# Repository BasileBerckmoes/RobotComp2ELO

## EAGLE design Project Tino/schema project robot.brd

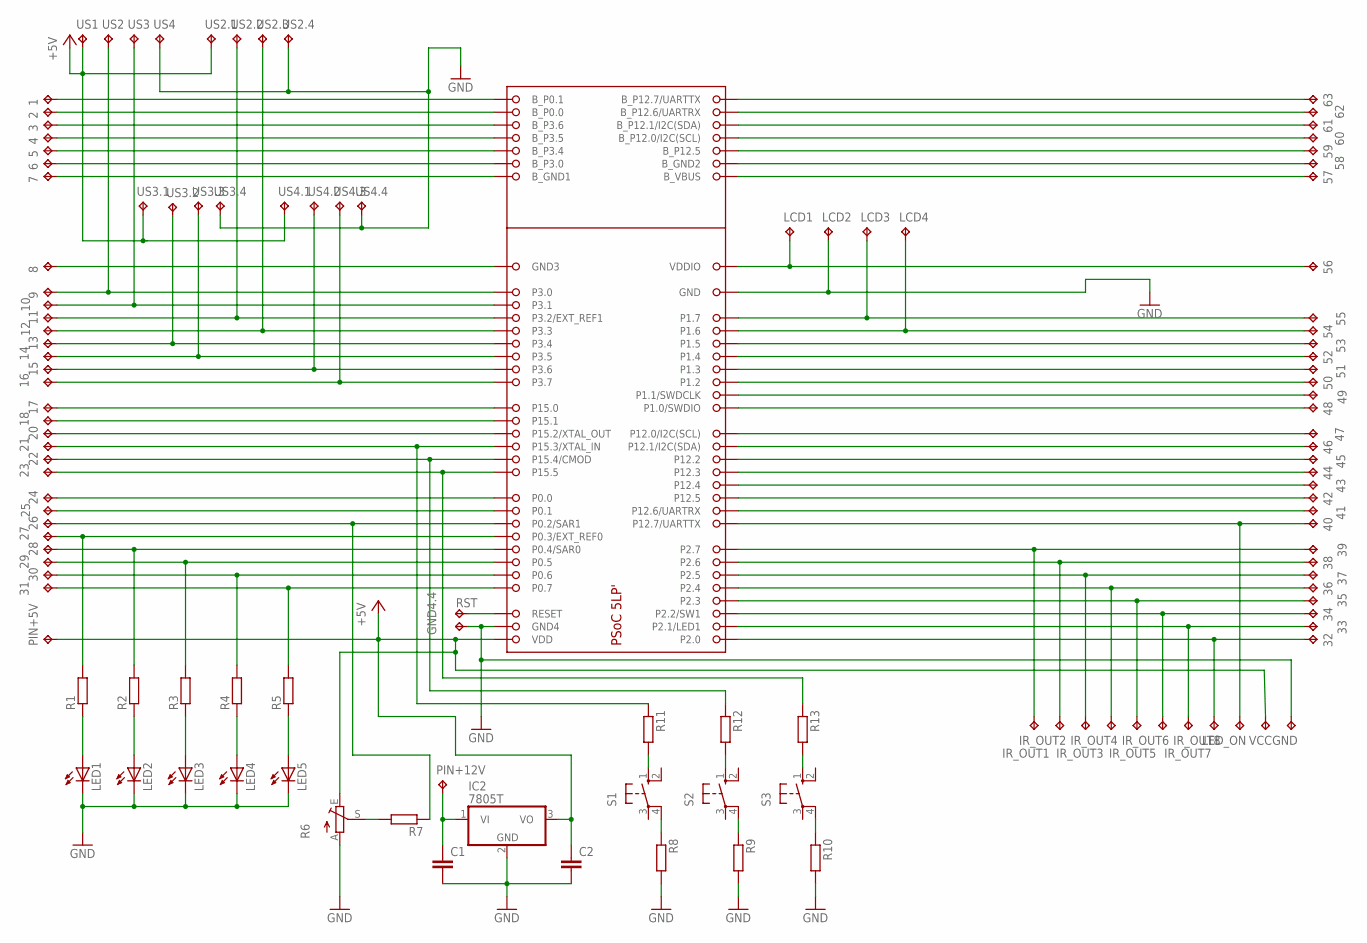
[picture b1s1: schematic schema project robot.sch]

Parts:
1, 2, 3, 4, 5, 6, 7, 8, 9, 10, 11, 12, 13, 14, 15, 16, 17, 18, 20, 21, 22, 23, 24, 25, 26, 27, 28, 29, 30, 31, 32, 33, 34, 35, 36, 37, 38, 39, 40, 41, 42, 43, 44, 45, 46, 47, 48, 49, 50, 51, 52, 53, 54, 55, 56, 57, 58, 59, 60, 61, 62, 63: TPPAD1-13Y; P1-13Y
C1, C2: C-EU050-035X075; C050-035X075
DEVICE1: CYPRESSFOOTPRINT_CYPRESS; CYPRESSFOOTPRINT_CYPRESSFOOTPRINT
GND, GND4.4: TPPAD1-13Y; P1-13Y
IC2: 7805T; TO220H
IR_OUT1, IR_OUT2, IR_OUT3, IR_OUT4, IR_OUT5, IR_OUT6, IR_OUT7, IR_OUT8: TPPAD1-13Y; P1-13Y
LCD1, LCD2, LCD3, LCD4: TPPAD1-13Y; P1-13Y
LED1, LED2, LED3, LED4, LED5: LED5MM
LED_ON: TPPAD1-13Y; P1-13Y
PIN+5V, PIN+12V: TPPAD1-13Y; P1-13Y
R1, R2, R3, R4, R5, R7, R8, R9, R10, R11, R12, R13: R-EU_0204/7; 0204/7
R6: TRIM_EU-CIP20C-6MM; CIP20C-6MM
RST: TPPAD1-13Y; P1-13Y
S1, S2, S3: 10-XX; B3F-10XX
US1, US2, US2.1, US2.2, US2.3, US2.4, US3, US3.1, US3.2, US3.3, US3.4, US4, US4.1, US4.2, US4.3, US4.4: TPPAD1-13Y; P1-13Y
VCC: TPPAD1-13Y; P1-13Y

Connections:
+5V: C2.1, DEVICE1.VVD (VDD), IC2.3 (VO), PIN+5V.TP, R6.E, US1.TP, US2.1.TP, US3.1.TP, US4.1.TP, VCC.TP
GND: C1.2, C2.2, DEVICE1.GND, DEVICE1.GND4, GND.TP, GND4.4.TP, IC2.2 (GND), LCD2.TP, LED1.K (C), LED2.K (C), LED3.K (C), LED4.K (C), LED5.K (C), R6.A, R8.2, R9.2, R10.2, US2.4.TP, US3.4.TP, US4.TP, US4.4.TP
unnamed: LED1.A, R1.1
unnamed: LED2.A, R2.1
unnamed: LED3.A, R3.1
unnamed: LED4.A, R4.1
unnamed: LED5.A, R5.1
unnamed: 31.TP, DEVICE1.P0.7, R5.2
unnamed: 30.TP, DEVICE1.P0.6, R4.2
unnamed: 29.TP, DEVICE1.P0.5, R3.2
unnamed: 25.TP, DEVICE1.P0.1
unnamed: 24.TP, DEVICE1.P0.0
unnamed: 1.TP, DEVICE1.B_P0.1
unnamed: 2.TP, DEVICE1.B_P0.0
unnamed: 3.TP, DEVICE1.B_P3.6
unnamed: 4.TP, DEVICE1.B_P3.5
unnamed: 5.TP, DEVICE1.B_P3.4
unnamed: 6.TP, DEVICE1.B_P3.0
unnamed: 7.TP, DEVICE1.B_GND1
unnamed: 8.TP, DEVICE1.GND3
unnamed: 9.TP, DEVICE1.P3.0, US2.TP
unnamed: 10.TP, DEVICE1.P3.1, US3.TP
unnamed: 11.TP, DEVICE1.P3.2 (P3.2/EXT_REF1), US2.2.TP
unnamed: 12.TP, DEVICE1.P3.3, US2.3.TP
unnamed: 16.TP, DEVICE1.P3.7, US4.3.TP
unnamed: 15.TP, DEVICE1.P3.6, US4.2.TP
unnamed: C1.1, IC2.1 (VI), PIN+12V.TP
unnamed: 14.TP, DEVICE1.P3.5, US3.3.TP
unnamed: 17.TP, DEVICE1.P15.0
unnamed: 18.TP, DEVICE1.P15.1
unnamed: 20.TP, DEVICE1.P15.2/XTAL_OUT
unnamed: 21.TP, DEVICE1.P15.3/XTAL_IN, R11.1
unnamed: 22.TP, DEVICE1.P15.4/CMOD, R12.1
unnamed: 23.TP, DEVICE1.P15.5, R13.1
unnamed: 26.TP, DEVICE1.P0.2/SAR1, R7.1
unnamed: 27.TP, DEVICE1.P0.3/EXT_REF0, R1.2
unnamed: 28.TP, DEVICE1.P0.4/SAR0, R2.2
unnamed: DEVICE1.RESET, RST.TP
unnamed: 13.TP, DEVICE1.P3.4, US3.2.TP
unnamed: 32.TP, DEVICE1.P2.0, IR_OUT8.TP
unnamed: 33.TP, DEVICE1.P2.1/LED1, IR_OUT7.TP
unnamed: 34.TP, DEVICE1.P2.2/SW1, IR_OUT6.TP
unnamed: 35.TP, DEVICE1.P2.3, IR_OUT5.TP
unnamed: 36.TP, DEVICE1.P2.4, IR_OUT4.TP
unnamed: 37.TP, DEVICE1.P2.5, IR_OUT3.TP
unnamed: 38.TP, DEVICE1.P2.6, IR_OUT2.TP
unnamed: 39.TP, DEVICE1.P2.7, IR_OUT1.TP
unnamed: 40.TP, DEVICE1.P12.7/UARTTX, LED_ON.TP
unnamed: 41.TP, DEVICE1.P12.6/UARTRX
unnamed: 42.TP, DEVICE1.P12.5
unnamed: 43.TP, DEVICE1.P12.4
unnamed: 44.TP, DEVICE1.P12.3
unnamed: 45.TP, DEVICE1.P12.2
unnamed: 46.TP, DEVICE1.P12.1/I2C(SDA)
unnamed: 47.TP, DEVICE1.P12.0/I2C(SCL)
unnamed: 48.TP, DEVICE1.P1.0/SWDIO
unnamed: 49.TP, DEVICE1.P1.1/SWDCLK
unnamed: 50.TP, DEVICE1.P1.2
unnamed: 51.TP, DEVICE1.P1.3
unnamed: 52.TP, DEVICE1.P1.4
unnamed: 53.TP, DEVICE1.P1.5
unnamed: 54.TP, DEVICE1.P1.6, LCD4.TP
unnamed: 55.TP, DEVICE1.P1.7, LCD3.TP
unnamed: R6.S, R7.2
unnamed: 57.TP, DEVICE1.B_VBUS
unnamed: 58.TP, DEVICE1.B_GND2
unnamed: 59.TP, DEVICE1.B_P12.5
unnamed: 60.TP, DEVICE1.B_12.0/I2C(SCL) (B_P12.0/I2C(SCL))
unnamed: 61.TP, DEVICE1.B_12.1/I2C(SDA) (B_P12.1/I2C(SDA))
unnamed: 62.TP, DEVICE1.B_12.6/UARTRX (B_P12.6/UARTRX)
unnamed: 63.TP, DEVICE1.B_12.7/UARTTX (B_P12.7/UARTTX)
unnamed: R8.1, S1.4 (P1)
unnamed: R9.1, S2.4 (P1)
unnamed: R10.1, S3.4 (P1)
unnamed: R13.2, S3.1 (S)
unnamed: R12.2, S2.1 (S)
unnamed: R11.2, S1.1 (S)
unnamed: 56.TP, DEVICE1.VDDIO, LCD1.TP

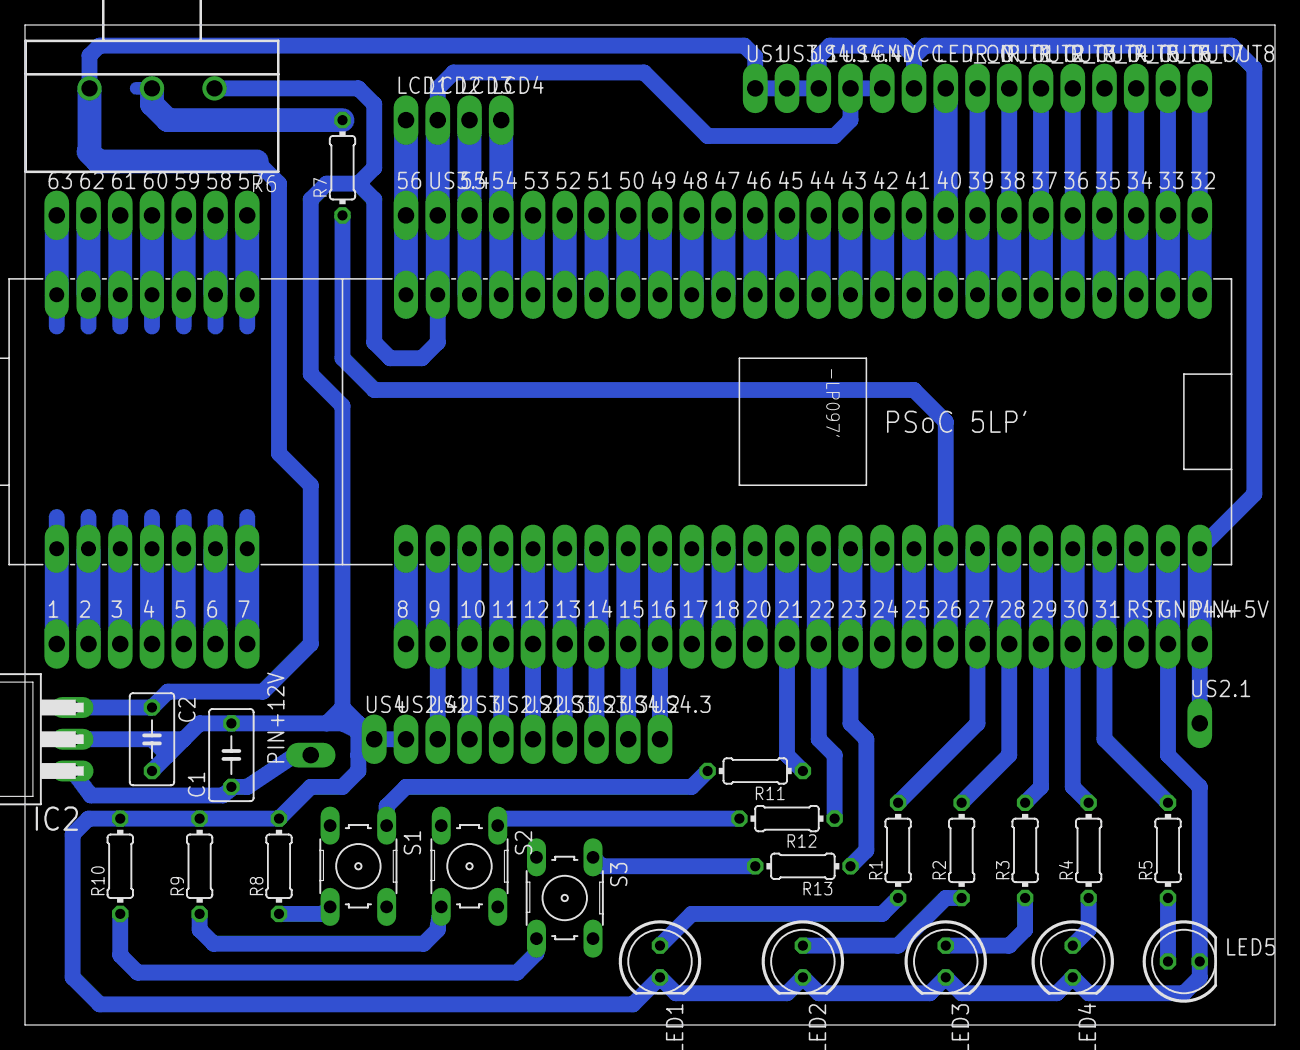
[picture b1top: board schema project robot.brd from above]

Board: 2 copper layers, 100.0 x 80.0 mm, 122 parts (0 on the bottom side), 78 nets.

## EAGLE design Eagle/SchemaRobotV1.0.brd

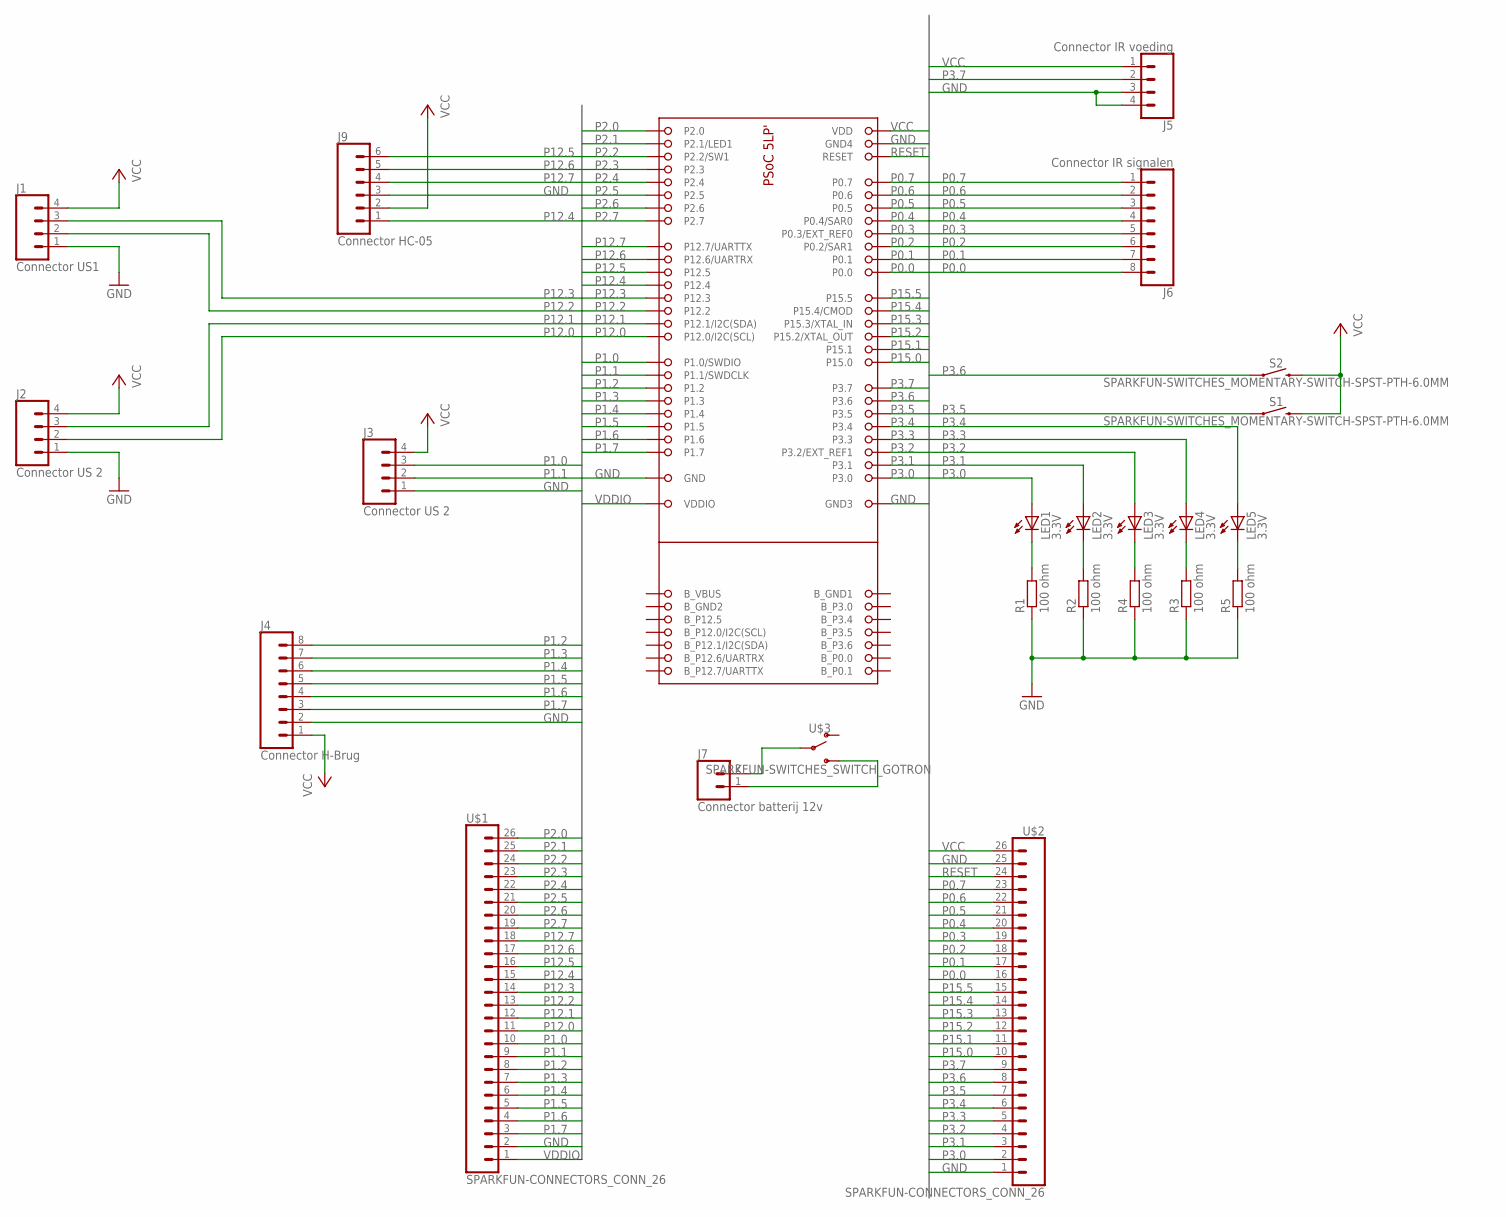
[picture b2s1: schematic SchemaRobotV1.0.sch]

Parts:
DEVICE1: CYPRESSFOOTPRINT_CYPRESS; CYPRESSFOOTPRINT_CYPRESSFOOTPRINT
J1: Connector US1; SPARKFUN-CONNECTORS_SCREWTERMINAL-3.5MM-4
J2, J3: Connector US 2; SPARKFUN-CONNECTORS_SCREWTERMINAL-3.5MM-4
J4: Connector H-Brug; SPARKFUN-CONNECTORS_SCREWTERMINAL-3.5MM-8
J5: Connector IR voeding; SPARKFUN-CONNECTORS_SCREWTERMINAL-3.5MM-4
J6: Connector IR signalen; SPARKFUN-CONNECTORS_SCREWTERMINAL-3.5MM-8
J7: Connector batterij 12v; SPARKFUN-CONNECTORS_SCREWTERMINAL-3.5MM-2
J9: Connector HC-05; SPARKFUN-CONNECTORS_1X06_LONGPADS
LED1, LED3, LED4, LED5: 3.3V; LED_LED5MM
LED2: 3.3V; LED5MM
R1, R2, R3, R4, R5: 100 ohm; EAGLE-LTSPICE_0204/7
S1, S2: SPARKFUN-SWITCHES_MOMENTARY-SWITCH-SPST-PTH-6.0MM; SPARKFUN-SWITCHES_TACTILE_SWITCH_PTH_6.0MM
U$1, U$2: SPARKFUN-CONNECTORS_CONN_26; SPARKFUN-CONNECTORS_1X26
U$3: SPARKFUN-SWITCHES_SWITCH_GOTRON; SPARKFUN-SWITCHES_SWITCH_SPDT_PTH_11.6X5.60MM

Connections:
GND: DEVICE1.GND, DEVICE1.GND3, DEVICE1.GND4, J1.1, J2.1, J3.1, J4.2, J5.3, J5.4, J9.3, R1.1, R2.1, R3.1, R4.1, R5.1, U$1.2, U$2.1, U$2.25
unnamed: J7.2, U$3.2
unnamed: LED1.K (C), R1.2
unnamed: LED2.K (C), R2.2
unnamed: LED3.K (C), R4.2
unnamed: LED4.K (C), R3.2
unnamed: LED5.K (C), R5.2
unnamed: J7.1, U$3.3 (S)
P0.0: DEVICE1.P0.0, J6.8, U$2.16
P0.1: DEVICE1.P0.1, J6.7, U$2.17
P0.2: DEVICE1.P0.2/SAR1, J6.6, U$2.18
P0.3: DEVICE1.P0.3/EXT_REF0, J6.5, U$2.19
P0.4: DEVICE1.P0.4/SAR0, J6.4, U$2.20
P0.5: DEVICE1.P0.5, J6.3, U$2.21
P0.6: DEVICE1.P0.6, J6.2, U$2.22
P0.7: DEVICE1.P0.7, J6.1, U$2.23
P1.0: DEVICE1.P1.0/SWDIO, J3.3, U$1.10
P1.1: DEVICE1.P1.1/SWDCLK, J3.2, U$1.9
P1.2: DEVICE1.P1.2, J4.8, U$1.8
P1.3: DEVICE1.P1.3, J4.7, U$1.7
P1.4: DEVICE1.P1.4, J4.6, U$1.6
P1.5: DEVICE1.P1.5, J4.5, U$1.5
P1.6: DEVICE1.P1.6, J4.4, U$1.4
P1.7: DEVICE1.P1.7, J4.3, U$1.3
P2.0: DEVICE1.P2.0, U$1.26
P2.1: DEVICE1.P2.1/LED1, U$1.25
P2.2: DEVICE1.P2.2/SW1, U$1.24
P2.3: DEVICE1.P2.3, U$1.23
P2.4: DEVICE1.P2.4, U$1.22
P2.5: DEVICE1.P2.5, U$1.21
P2.6: DEVICE1.P2.6, U$1.20
P2.7: DEVICE1.P2.7, U$1.19
P3.0: DEVICE1.P3.0, LED1.A, U$2.2
P3.1: DEVICE1.P3.1, LED2.A, U$2.3
P3.2: DEVICE1.P3.2 (P3.2/EXT_REF1), LED3.A, U$2.4
P3.3: DEVICE1.P3.3, LED4.A, U$2.5
P3.4: DEVICE1.P3.4, LED5.A, U$2.6
P3.5: DEVICE1.P3.5, S1.1, U$2.7
P3.6: DEVICE1.P3.6, S2.1, U$2.8
P3.7: DEVICE1.P3.7, J5.2, U$2.9
P12.0: DEVICE1.P12.0/I2C(SCL), J2.2, U$1.11
P12.1: DEVICE1.P12.1/I2C(SDA), J2.3, U$1.12
P12.2: DEVICE1.P12.2, J1.2, U$1.13
P12.3: DEVICE1.P12.3, J1.3, U$1.14
P12.4: DEVICE1.P12.4, J9.1, U$1.15
P12.5: DEVICE1.P12.5, J9.6, U$1.16
P12.6: DEVICE1.P12.6/UARTRX, J9.5, U$1.17
P12.7: DEVICE1.P12.7/UARTTX, J9.4, U$1.18
P15.0: DEVICE1.P15.0, U$2.10
P15.1: DEVICE1.P15.1, U$2.11
P15.2: DEVICE1.P15.2/XTAL_OUT, U$2.12
P15.3: DEVICE1.P15.3/XTAL_IN, U$2.13
P15.4: DEVICE1.P15.4/CMOD, U$2.14
P15.5: DEVICE1.P15.5, U$2.15
RESET: DEVICE1.RESET, U$2.24
VCC: DEVICE1.VVD (VDD), J1.4, J2.4, J3.4, J4.1, J5.1, J9.2, S1.3 (2), S2.3 (2), U$2.26
VDDIO: DEVICE1.VDDIO, U$1.1

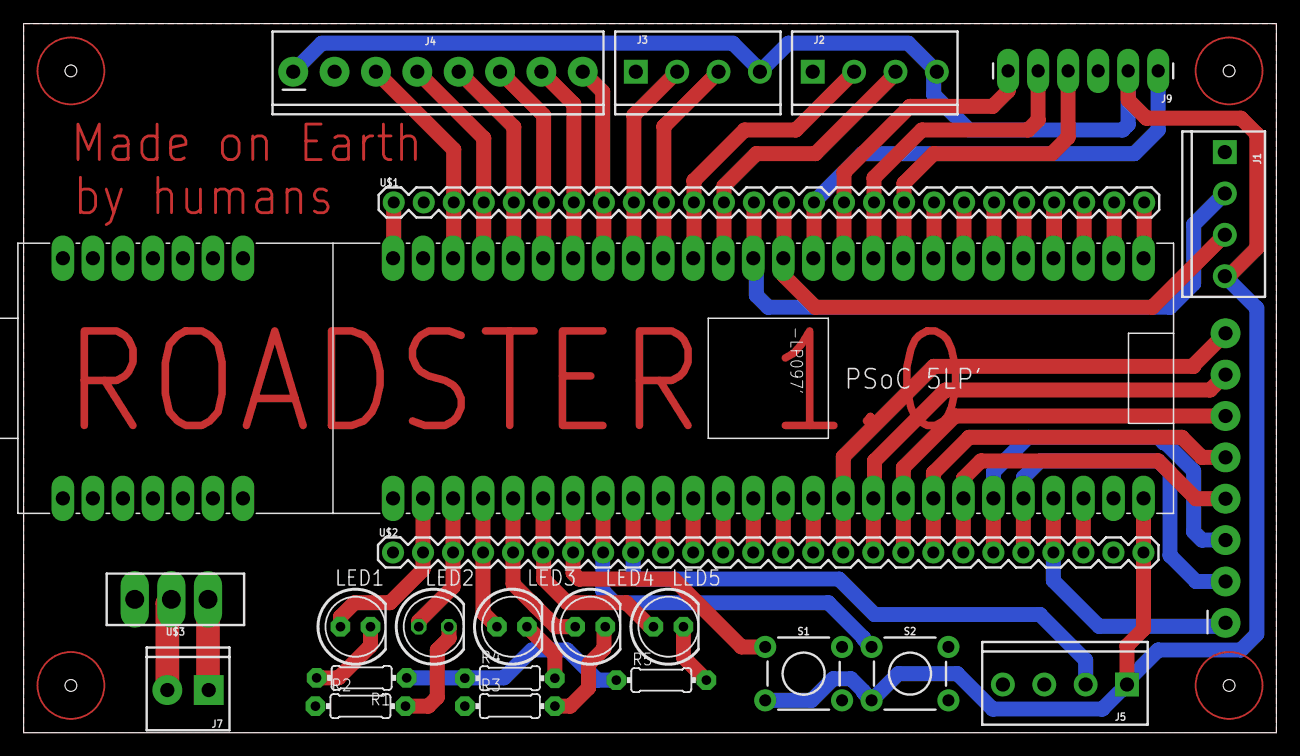
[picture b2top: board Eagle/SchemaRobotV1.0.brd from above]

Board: 2 copper layers, 106.0 x 60.0 mm, 24 parts (1 on the bottom side), 57 nets.

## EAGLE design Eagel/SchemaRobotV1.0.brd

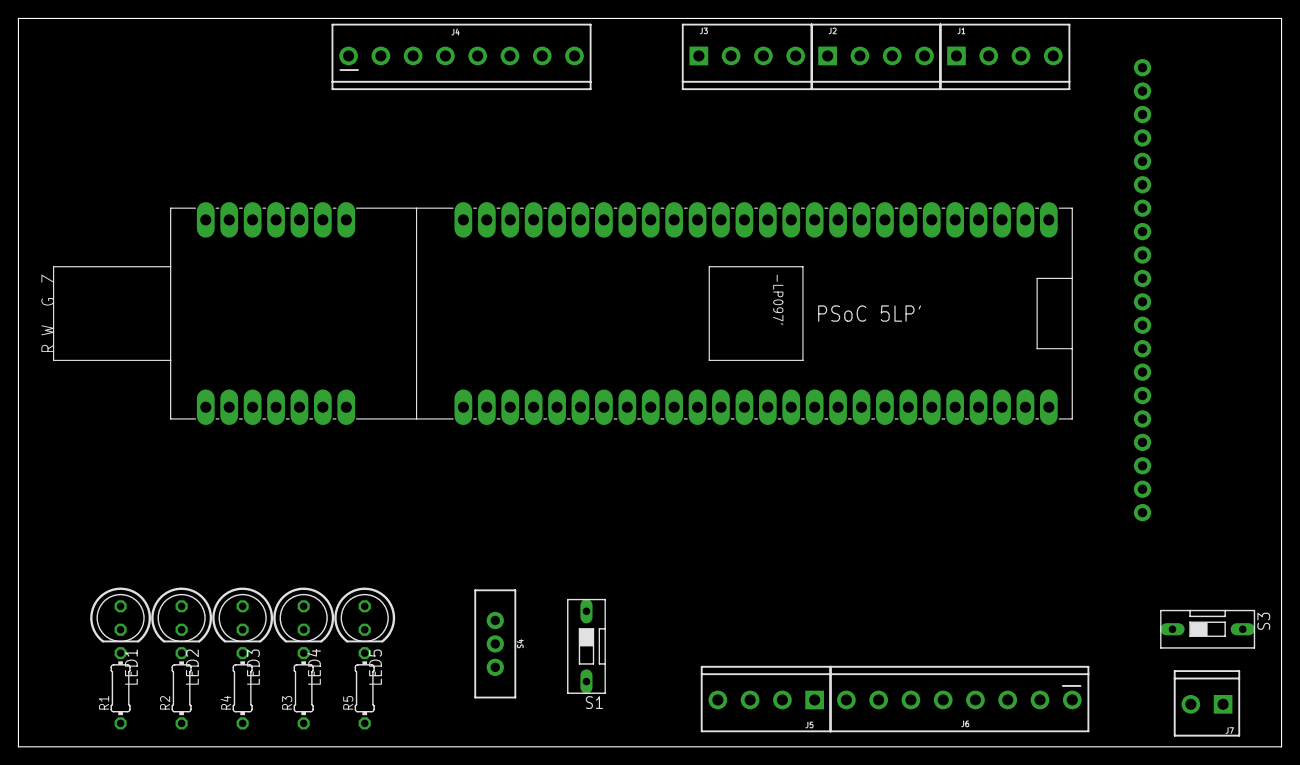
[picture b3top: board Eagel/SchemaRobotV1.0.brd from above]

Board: 2 copper layers, 137.0 x 79.0 mm, 22 parts (1 on the bottom side), 44 nets, no tracks yet.

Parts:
DEVICE1: CYPRESSFOOTPRINT_CYPRESS; CYPRESSFOOTPRINT_CYPRESSFOOTPRINT
J1: Connector US1; SCREWTERMINAL-3.5MM-4
J2, J3: Connector US 2; SCREWTERMINAL-3.5MM-4
J4: Connector H-Brug; SCREWTERMINAL-3.5MM-8
J5: Connector IR voeding; SCREWTERMINAL-3.5MM-4
J6: Connector IR signalen; SCREWTERMINAL-3.5MM-8
J7: Connector batterij 12v; SCREWTERMINAL-3.5MM-2
J8: Connector LCD; 1X20
LED1, LED2, LED3, LED4, LED5: LED5MM
R1, R2, R3, R4, R5: 100 ohm; 0204/7
S1, S3: DS-01
S4: SWITCH_SPDT_PTH_11.6X4.0MM

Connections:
ECHO1: DEVICE1.P12.3, J1.3
ECHO2: DEVICE1.P12.1/I2C(SDA), J2.3
ECHO3: DEVICE1.P1.0/SWDIO, J3.3
ENA: DEVICE1.P1.2, J4.8
ENB: DEVICE1.P1.7, J4.3
GND: DEVICE1.GND, DEVICE1.GND3, DEVICE1.GND4, J1.1, J2.1, J3.1, J4.2, J5.3, J5.4, J8.1, J8.3, R1.1, R2.1, R3.1, R4.1, R5.1, S4.3
IN1: DEVICE1.P1.3, J4.7
IN2: DEVICE1.P1.4, J4.6
IN3: DEVICE1.P1.5, J4.5
IN4: DEVICE1.P1.6, J4.4
IRS1: DEVICE1.P0.7, J6.1
IRS2: DEVICE1.P0.6, J6.2
IRS3: DEVICE1.P0.5, J6.3
IRS4: DEVICE1.P0.4/SAR0, J6.4
IRS5: DEVICE1.P0.3/EXT_REF0, J6.5
IRS6: DEVICE1.P0.2/SAR1, J6.6
IRS7: DEVICE1.P0.1, J6.7
IRS8: DEVICE1.P0.0, J6.8
LED1: DEVICE1.P3.0, LED1.A
LED2: DEVICE1.P3.1, LED2.A
LED3: DEVICE1.P3.2, LED3.A
LED4: DEVICE1.P3.3, LED4.A
LED5: DEVICE1.P3.4, LED5.A
LEDON: DEVICE1.P3.7, J5.2
unnamed: DEVICE1.P2.3, J8.14
unnamed: LED1.K, R1.2
unnamed: LED2.K, R2.2
unnamed: LED3.K, R4.2
unnamed: LED4.K, R3.2
unnamed: LED5.K, R5.2
unnamed: DEVICE1.P2.2/SW1, J8.13
unnamed: DEVICE1.P2.1/LED1, J8.12
unnamed: DEVICE1.P2.0, J8.11
unnamed: DEVICE1.P2.4, J8.6
unnamed: DEVICE1.P2.6, J8.5
unnamed: DEVICE1.P2.5, J8.4
unnamed: J7.2, S3.1
unnamed: J7.1, S3.2
SW1: DEVICE1.P3.5, S4.2
SW2: DEVICE1.P3.6, S1.1
TRIG1: DEVICE1.P12.2, J1.2
TRIG2: DEVICE1.P12.0/I2C(SCL), J2.2
TRIG3: DEVICE1.P1.1/SWDCLK, J3.2
VCC: DEVICE1.VVD, J1.4, J2.4, J3.4, J4.1, J5.1, J8.2, S1.2, S4.1

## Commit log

2018-02-16 readme
    added readme
2018-02-16 init
    Map testversie code en map verslag toegevoegd
2018-02-16 test
    niks
2018-02-16 testen
    Voorbeeld programma toegevoegd voor uitlezen van afstands sensoren
2018-02-19 Schema's
    L298N toegevoegd
2018-02-19 Test version arduino
    Timer interupt toegevoegd
2018-02-19 Bluetooth
    Projectvoorstel
2018-02-19 Test version
    programma aangepast inlezen sensoren
2018-02-26 Psoc
    Toevoegen keuze processor image
2018-02-26 werk maandag
2018-02-26 test version psoc
2018-02-28 Verslag
    verslag geupdate
2018-03-04 eagel
    start design schema
2018-03-05 schema
    schema bijna af
2018-03-05 Datasheet
    LCD
2018-03-06 eagle
    schema
2018-03-07 eagle
    update schema
2018-03-07 eagle
    connectoren vervangen
2018-03-07 eagle
    schema bijna af!
2018-03-10 psoc
    schema voeding pinnen
2018-03-10 eagle
    schema klaar, nu pcb nog
2018-03-10 eagle
    pcb bijna af
2018-03-10 eagle
    bijna klaar!
2018-03-11 eagle
    meer padjes van top naar bottom
2018-03-11 eagle
    padjes verbeterd
2018-03-12 git opkuis
    mappenstructuur aangepast
2018-03-12 git opkuis
    structuur
2018-03-12 psoc
    main programma gestart
2018-03-12 software
    sensors binar uitlezen op lcd gestart
2018-03-13 roadster
    ir sensoren werken
2018-03-19 roadster
    programma
2018-03-19 roadster
    us werkt
2018-03-19 Planning
    planning
2018-03-19 Comments
2018-03-26 roadster
    veel software verbeteringen
2018-03-27 roadster
    fix
2018-03-28 ble
    prutsen
2018-03-28 Robot
    Mediaan
2018-03-28 ble
    commit
2018-03-28 ble
    module antwoord!!
2018-03-29 ble
    update
2018-03-29 ble
    communicatie werkt !!!
2018-03-30 roadster
    ITS ALIVE
2018-03-30 bleTest
    test compele
2018-03-30 .
    .
2018-04-01 wtf
    wtf
2018-04-01 ble
    command update
2018-04-01 roadster
    added ble
2018-04-02 ble + roadster
    communicatie on point!!
2018-04-03 roadster
    code opgekuist
2018-04-04 roadster
    testinf fase1
2018-04-04 roadster
    eerste geslaagde test!!!
2018-04-04 einde
    einde sessie
2018-04-06 raodster uitlegsessie
    done
2018-04-08 Joystick experiment
    Proberen de waarden van de joystick goed te zetten
2018-04-15 Lijnvolger check en joystick
2018-04-16 Proberen met switch
2018-04-19 verbeteringenH2
2018-04-20 Edit software -> werkt niet volledig
2018-04-21 ble
    not working
2018-04-21 roadster
    raceversie
2018-04-21 roadster
    racelogica IR filter toegevoegd
2018-04-21 waarheidstabel
    waarheidstabel opgemaakt
2018-04-23 roadster
    improvements
2018-04-24 roadster
    timer update
2018-04-24 roadster
    update
2018-04-24 roadster
    einde robot sessie ugent
2018-04-25 roadster
    einde sessie
2018-04-26 roadster
2018-04-27 roadster
    raar probleem
2018-04-27 roadster
    complete!
2018-04-30 roadster
    dynamisch rijden
2018-05-01 FINAL
    final version foutloos
2018-05-01 final
    final version na test sessie
2018-05-10 afstandsbediening klaar
2018-05-10 verslag ble klaar
2018-05-13 verslag nog eens nagelezen
2018-05-21 Ddijd
2018-05-24 Verslag bluetooth ready
2018-06-02 poster
2018-06-10 poster af
2018-06-12 added tino

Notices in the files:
parts and their libraries:
SparkFun-Connectors: Licensing: Creative Commons ShareAlike 4.0 International - https://creativecommons.org/licenses/by-sa/4.0
